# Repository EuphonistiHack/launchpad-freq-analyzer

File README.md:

launchpad-freq-analyzer
===============================================================================

Project code for an fft based graphic equalizer to be run on a Stellaris
Launchpad.

I'm assuming that TI will follow the standard procedure for Stellaris installs
for Launchpad, which is to say that when you install StellarisWare, the file
structure will be such that you have a root (defaulted to C:/StellarisWare) in
which driverlib will be copied.  That root will also contain a  boards
directory, which in turn should contain a directory for the lm4f120.  If you do
a git clone off of the above address, you'll find a similar file structure.
You should just be able to copy the led_equalizer project into the lm4f120
board directory, and copy dsplib into the stellarisWare root.

In it's current state, the only thing I've verified working is the Code
Composer Studio build.  I have included project files that should at least be
95% good for all the other Stellaris supported environments: a makefile for you
command line GCC enthusiasts and project files for Keil uVision, IAR Embedded
Workbench, and CodeSourcery's IDE.  I'm guessing that if you tried to import
and build into any of those as is, you will hit two problems. 

For one, there's a config array that the uDMA engine uses that needs to be
stored on a 1024 byte boundary.  I have some pragmas in place to handle that
for CCS and IAR, but I haven't yet figured out the syntax for handling this in
other compilers.  Shouldn't be too hard to figure out, and hopefully I'll have
that done soon.

The second issue will be with the CMSIS library.  The current release contains
a precompiled .lib and the headers necessary to interface with it.  This was
compiled with the tms470 compiler, though, so it won't work with anything other
than CCS.  If you download CMSIS for yourself, it should come with precompiled
binaries for use with uVision, GCC, and CodeSourcery.  You'll want to add those
to dsplib, then edit your project's library include path/list to point to the
proper binary.  I am considering including these in dsplib, but I'm not really
sure what ARM's policy is on redistributing their binaries, and I'd prefer not
get sued out of existence :)

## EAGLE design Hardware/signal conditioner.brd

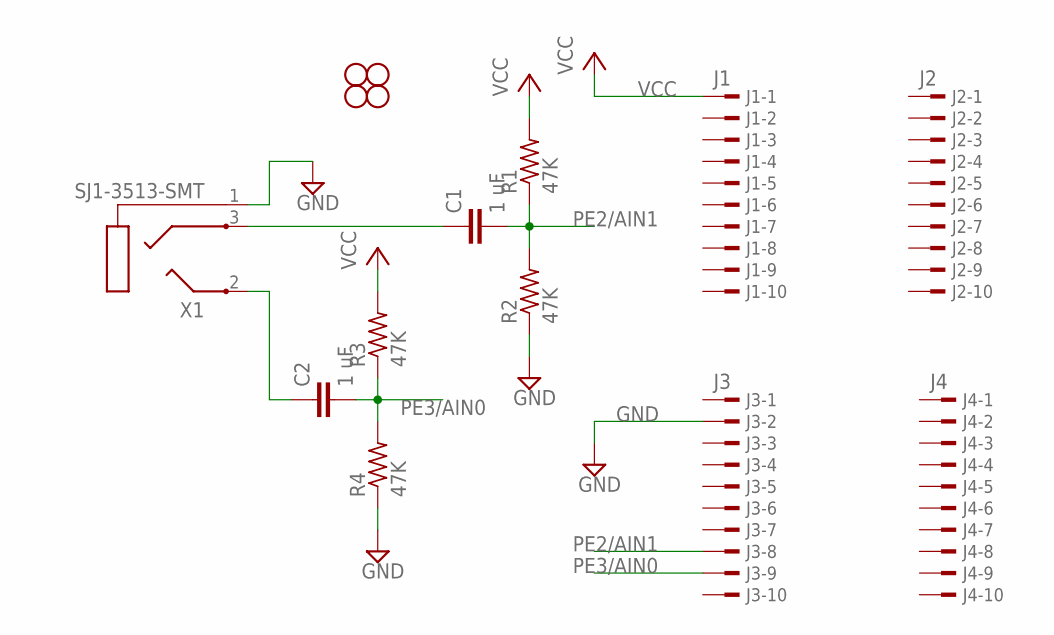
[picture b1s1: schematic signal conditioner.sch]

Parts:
C1, C2: 1 uF; C050-025X075
J1: J1; TSW-110-02-S-S
J2: J2; TSW-110-02-S-S
J3: J3; TSW-110-02-S-S
J4: J4; TSW-110-02-S-S
JP1, JP2, JP3, JP4: STAND-OFF
R1, R2, R3, R4: 47K; 0207/7
X1: SJ1-3513-SMT; 3513

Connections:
GND: J3.2, R2.1, R4.1, X1.1 (EARTH)
unnamed: C1.1, X1.3 (RING)
unnamed: C2.1, X1.2 (TIP)
PE2/AIN1: C1.2, J3.8, R1.1, R2.2
PE3/AIN0: C2.2, J3.9, R3.1, R4.2
VCC: J1.1, R1.2, R3.2

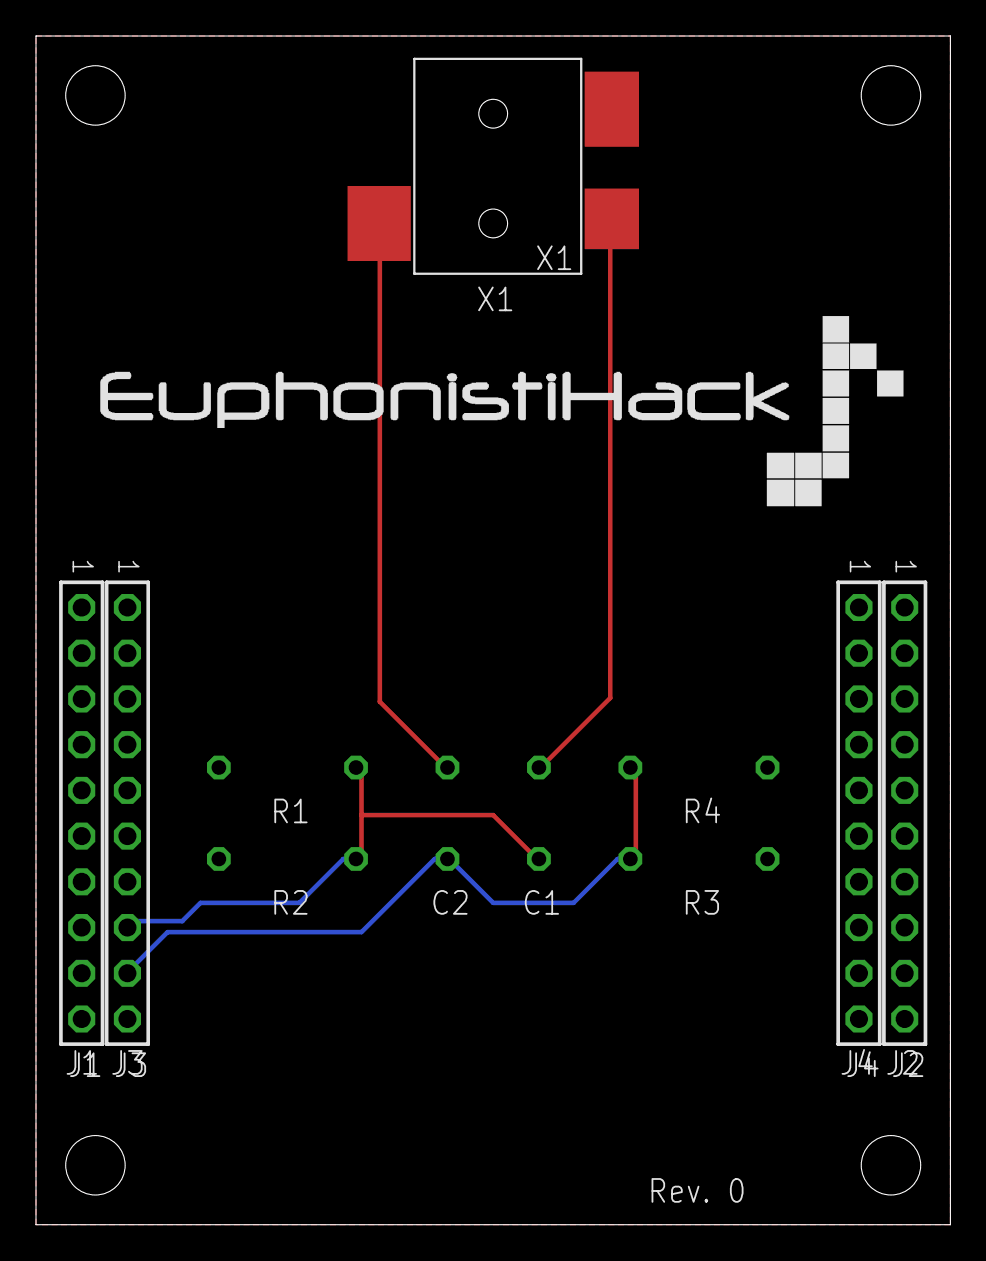
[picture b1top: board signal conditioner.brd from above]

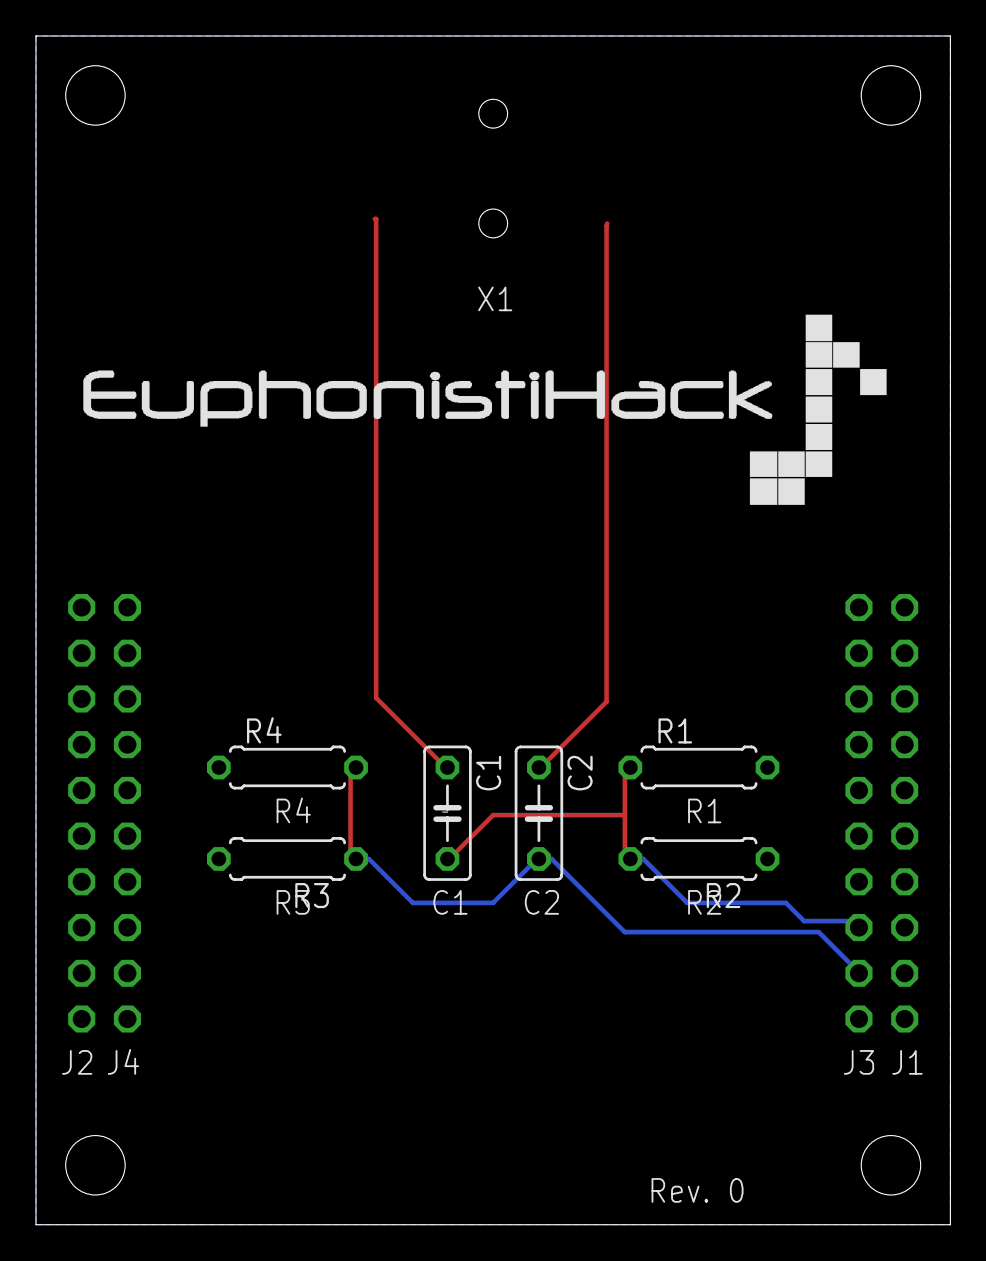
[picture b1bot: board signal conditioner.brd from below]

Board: 2 copper layers, 50.8 x 66.0 mm, 15 parts (6 on the bottom side), 6 nets.

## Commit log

2012-09-09 Add in EVERYTHING
    This should work at least for CCS. Project files are in place for all the other
    builds, and the makefile's in there for GCC, but the library paths aren't
    verified for anything other than CCS at the moment. I'm guessing if you tried
    to build it in another environment, it would bork, but would be easy to fix by
    manually adding a library path to the cmsis.lib for that compiler.
2012-09-09 Added some usage details/explanation to README
2012-12-15 Added new project for use with kentec booster pack Added board files for custom audio capture board

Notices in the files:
parts and their libraries:
SparkFun: Licensing: CC v3.0 Share-Alike You are welcome to use this library for commercial purposes.
